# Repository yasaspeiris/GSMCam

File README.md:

# GSMCam
A Python program to determine the Grams per Square Meter of a Fabric using hardware accelerated Image Processing
(Also contains source code, design files and PCB schematics for cartesian slider system used to move the camera across fabrics.)

Conventional method of fabric GSM measurement involves cutting a small round piece of fabric with an area of 0.01 square centimeters and measuring its weight using a precision balance.This project was aimed to replace this conventional method with an optical based one. Currently the scope of the project is limited to single light color (white) fabrics with a plain, twill weave. (Algorithm can also be applied to knit fabrics with a considerable accuracy as well)

For anyone looking to implement a hardware accelerated application with minimal development and debugging time, PYNQ is a great option. Currently PYNQ supports several boards including the Ultra96. The computer vision library for PYNQ provides several overlays for accelerating OpenCV functions in hardware. Currently Filter2D and dilation operations are supported. 

The following flow diagram depicts the stages in the GSM Determination process.

The GUI is made using Flask, and can be used to calibrate and view results.

### Complete Instructions : 
https://www.hackster.io/yasaspeiris/fabric-gsm-determination-using-ultra96-pynq-6c5499

### Contributors : 

Pasindu Liyanage

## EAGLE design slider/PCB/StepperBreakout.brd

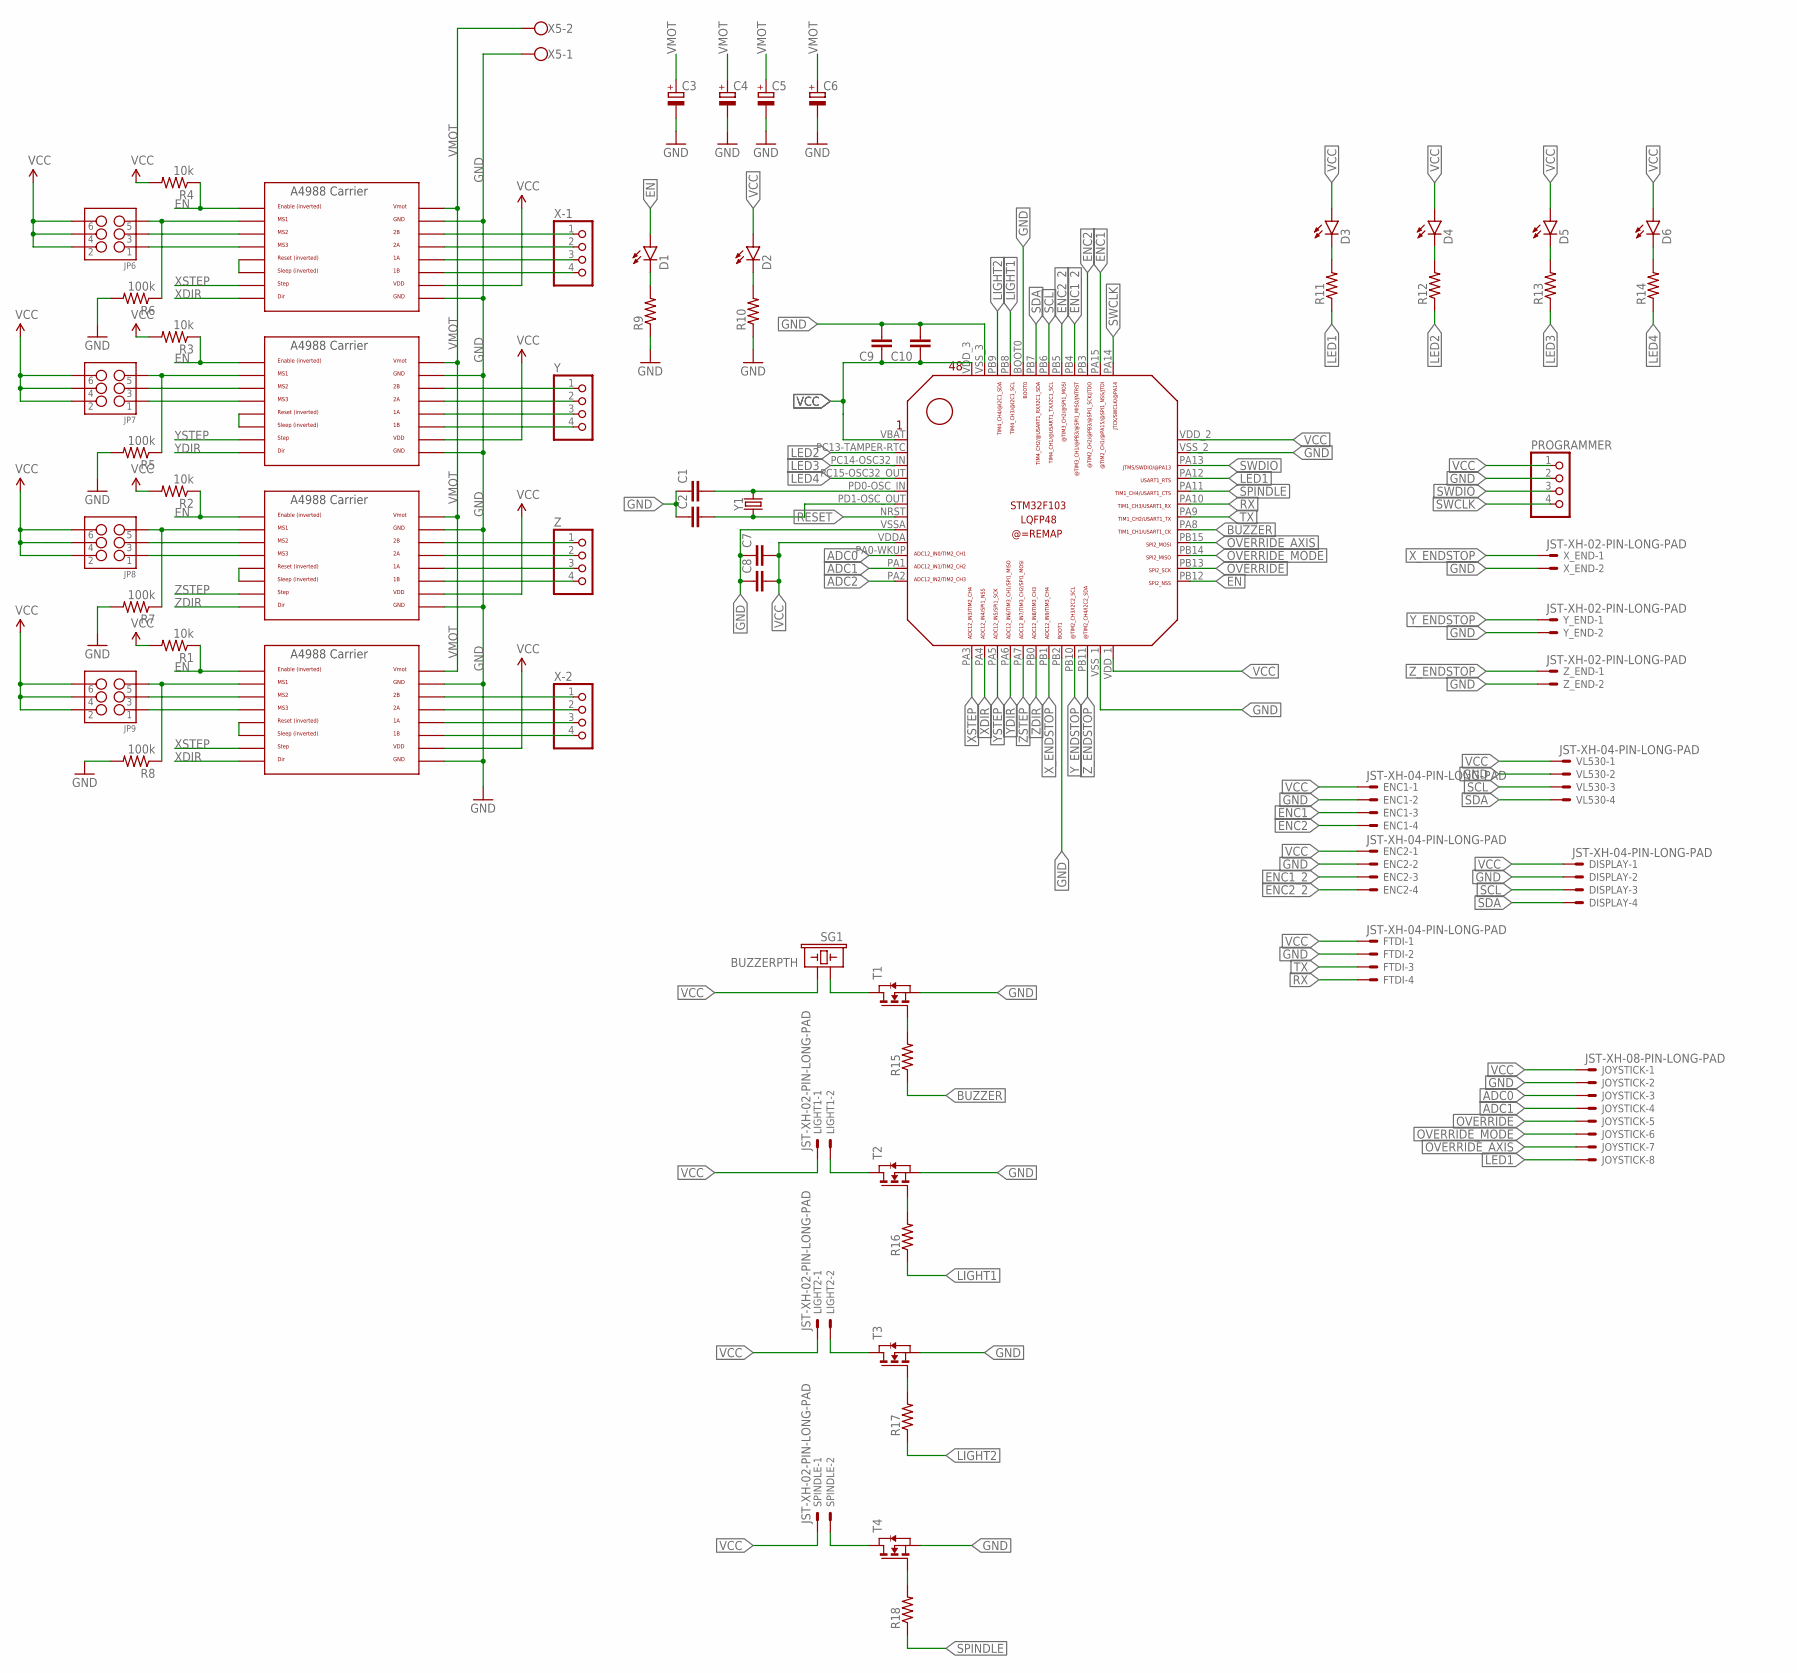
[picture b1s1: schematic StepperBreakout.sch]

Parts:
C1, C2, C7, C8, C9, C10: C-EUC0805; C0805
C3, C4, C5, C6: CPOL-EUE5-8.5; E5-8,5
D1, D2, D3, D4, D5, D6: LED0603; LED-0603
DISPLAY: JST-XH-04-PIN-LONG-PAD; JST-XH-04-PACKAGE-LONG-PAD
ENC1, ENC2: JST-XH-04-PIN-LONG-PAD; JST-XH-04-PACKAGE-LONG-PAD
FTDI: JST-XH-04-PIN-LONG-PAD; JST-XH-04-PACKAGE-LONG-PAD
JOYSTICK: JST-XH-08-PIN-LONG-PAD; JST-XH-08-PACKAGE-LONG-PAD
JP6, JP7, JP8, JP9: M03X2NO_SILK; 2X3-NS
LIGHT1, LIGHT2: JST-XH-02-PIN-LONG-PAD; JST-XH-02-PACKAGE-LONG-PAD
PROGRAMMER: PINHD-1X4; 1X04
R1, R2, R3, R4: 10k; 0805
R5, R6, R7, R8: 100k; 0805
R9, R10, R11, R12, R13, R14, R15, R16, R17, R18: RESISTOR0805-RES; 0805
SG1: BUZZERPTH; BUZZER-12MM
SPINDLE: JST-XH-02-PIN-LONG-PAD; JST-XH-02-PACKAGE-LONG-PAD
T1, T2, T3, T4: NMOSSOT23; SOT-23
U$1, U$2, U$3, U$4: POLOLU_A4983CARRIER; A4988BREAKOUT
U$5: STM32F103_LQFP48
VL530: JST-XH-04-PIN-LONG-PAD; JST-XH-04-PACKAGE-LONG-PAD
X5: W237-102
X-1, X-2: PINHD-1X4; 1X04
X_END: JST-XH-02-PIN-LONG-PAD; JST-XH-02-PACKAGE-LONG-PAD
Y: PINHD-1X4; 1X04
Y1: CRYSTALPTH-HC49UV; HC49U
Y_END: JST-XH-02-PIN-LONG-PAD; JST-XH-02-PACKAGE-LONG-PAD
Z: PINHD-1X4; 1X04
Z_END: JST-XH-02-PIN-LONG-PAD; JST-XH-02-PACKAGE-LONG-PAD

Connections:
ADC0: JOYSTICK.3, U$5.PA0-WKUP
ADC1: JOYSTICK.4, U$5.PA1
ADC2: U$5.PA2
BUZZER: R15.1, U$5.PA8
EN: D1.A, R1.1, R2.1, R3.1, R4.1, U$1.EN, U$2.EN, U$3.EN, U$4.EN, U$5.PB12
ENC1: ENC1.3, U$5.PA15
ENC1_2: ENC2.3, U$5.PB4
ENC2: ENC1.4, U$5.PB3
ENC2_2: ENC2.4, U$5.PB5
GND: C1.1, C2.1, C3.-, C4.-, C5.-, C6.-, C7.1, C8.1, C9.2, C10.2, DISPLAY.2, ENC1.2, ENC2.2, FTDI.2, JOYSTICK.2, PROGRAMMER.2, R5.2, R6.2, R7.2, R8.2, R9.1, R10.1, T1.2 (S), T2.2 (S), T3.2 (S), T4.2 (S), U$1.GND, U$1.GND@0 (GND), U$2.GND, U$2.GND@0 (GND), U$3.GND, U$3.GND@0 (GND), U$4.GND, U$4.GND@0 (GND), U$5.BOOT0, U$5.PB2, U$5.VSSA, U$5.VSS_1, U$5.VSS_2, U$5.VSS_3, VL530.2, X5.1, X_END.2, Y_END.2, Z_END.2
LED1: JOYSTICK.8, R11.1, U$5.PA12
LED2: R12.1, U$5.PC13-TAMPER-RTC
LED3: R13.1, U$5.PC14-OSC32_IN
LED4: R14.1, U$5.PC15-OSC32_OUT (PC15-OSC_OUT)
LIGHT1: R16.1, U$5.PB8
LIGHT2: R17.1, U$5.PB9
unnamed: U$3.1B, Y.4
unnamed: U$3.1A, Y.3
unnamed: U$3.2A, Y.2
unnamed: U$3.2B, Y.1
unnamed: U$1.2B, Z.1
unnamed: U$1.2A, Z.2
unnamed: U$1.1A, Z.3
unnamed: U$1.1B, Z.4
unnamed: U$2.2B, X-2.1
unnamed: U$2.2A, X-2.2
unnamed: U$2.1A, X-2.3
unnamed: U$2.1B, X-2.4
unnamed: U$4.2B, X-1.1
unnamed: U$4.2A, X-1.2
unnamed: U$4.1A, X-1.3
unnamed: U$4.1B, X-1.4
unnamed: JP6.5, R6.1, U$4.MS1
unnamed: JP6.3, U$4.MS2
unnamed: JP6.1, U$4.MS3
unnamed: JP7.5, R5.1, U$3.MS1
unnamed: JP7.3, U$3.MS2
unnamed: JP7.1, U$3.MS3
unnamed: JP8.5, R7.1, U$1.MS1
unnamed: JP8.3, U$1.MS2
unnamed: JP8.1, U$1.MS3
unnamed: JP9.5, R8.1, U$2.MS1
unnamed: JP9.3, U$2.MS2
unnamed: JP9.1, U$2.MS3
unnamed: C1.2, U$5.PD0-OSC_IN, Y1.2
unnamed: D1.C, R9.2
unnamed: D2.C, R10.2
unnamed: C2.2, U$5.PD1-OSC_OUT, Y1.1
unnamed: U$2.RST, U$2.SLP (SLEEP)
unnamed: U$1.RST, U$1.SLP (SLEEP)
unnamed: U$3.RST, U$3.SLP (SLEEP)
unnamed: U$4.RST, U$4.SLP (SLEEP)
unnamed: D3.C, R11.2
unnamed: D4.C, R12.2
unnamed: D5.C, R13.2
unnamed: D6.C, R14.2
unnamed: SG1.+ (1), T1.1 (D)
unnamed: R15.2, T1.3 (G)
unnamed: LIGHT1.2, T2.1 (D)
unnamed: R16.2, T2.3 (G)
unnamed: LIGHT2.2, T3.1 (D)
unnamed: R17.2, T3.3 (G)
unnamed: SPINDLE.2, T4.1 (D)
unnamed: R18.2, T4.3 (G)
OVERRIDE: JOYSTICK.5, U$5.PB13
OVERRIDE_AXIS: JOYSTICK.7, U$5.PB15
OVERRIDE_MODE: JOYSTICK.6, U$5.PB14
RESET: U$5.NRST
RX: FTDI.4, U$5.PA10
SCL: DISPLAY.3, U$5.PB6, VL530.3
SDA: DISPLAY.4, U$5.PB7, VL530.4
SPINDLE: R18.1, U$5.PA11
SWCLK: PROGRAMMER.4, U$5.PA14
SWDIO: PROGRAMMER.3, U$5.PA13
TX: FTDI.3, U$5.PA9
VCC: C7.2, C8.2, C9.1, C10.1, D2.A, D3.A, D4.A, D5.A, D6.A, DISPLAY.1, ENC1.1, ENC2.1, FTDI.1, JOYSTICK.1, JP6.2, JP6.4, JP6.6, JP7.2, JP7.4, JP7.6, JP8.2, JP8.4, JP8.6, JP9.2, JP9.4, JP9.6, LIGHT1.1, LIGHT2.1, PROGRAMMER.1, R1.2, R2.2, R3.2, R4.2, SG1.- (2), SPINDLE.1, U$1.VDD, U$2.VDD, U$3.VDD, U$4.VDD, U$5.VBAT, U$5.VDDA, U$5.VDD_1, U$5.VDD_2, U$5.VDD_3, VL530.1
VMOT: C3.+, C4.+, C5.+, C6.+, U$1.VMOT, U$2.VMOT, U$3.VMOT, U$4.VMOT, X5.2
XDIR: U$2.DIR, U$4.DIR, U$5.PA4
XSTEP: U$2.STEP, U$4.STEP, U$5.PA3
X_ENDSTOP: U$5.PB1, X_END.1
YDIR: U$3.DIR, U$5.PA6
YSTEP: U$3.STEP, U$5.PA5
Y_ENDSTOP: U$5.PB10, Y_END.1
ZDIR: U$1.DIR, U$5.PB0
ZSTEP: U$1.STEP, U$5.PA7
Z_ENDSTOP: U$5.PB11, Z_END.1

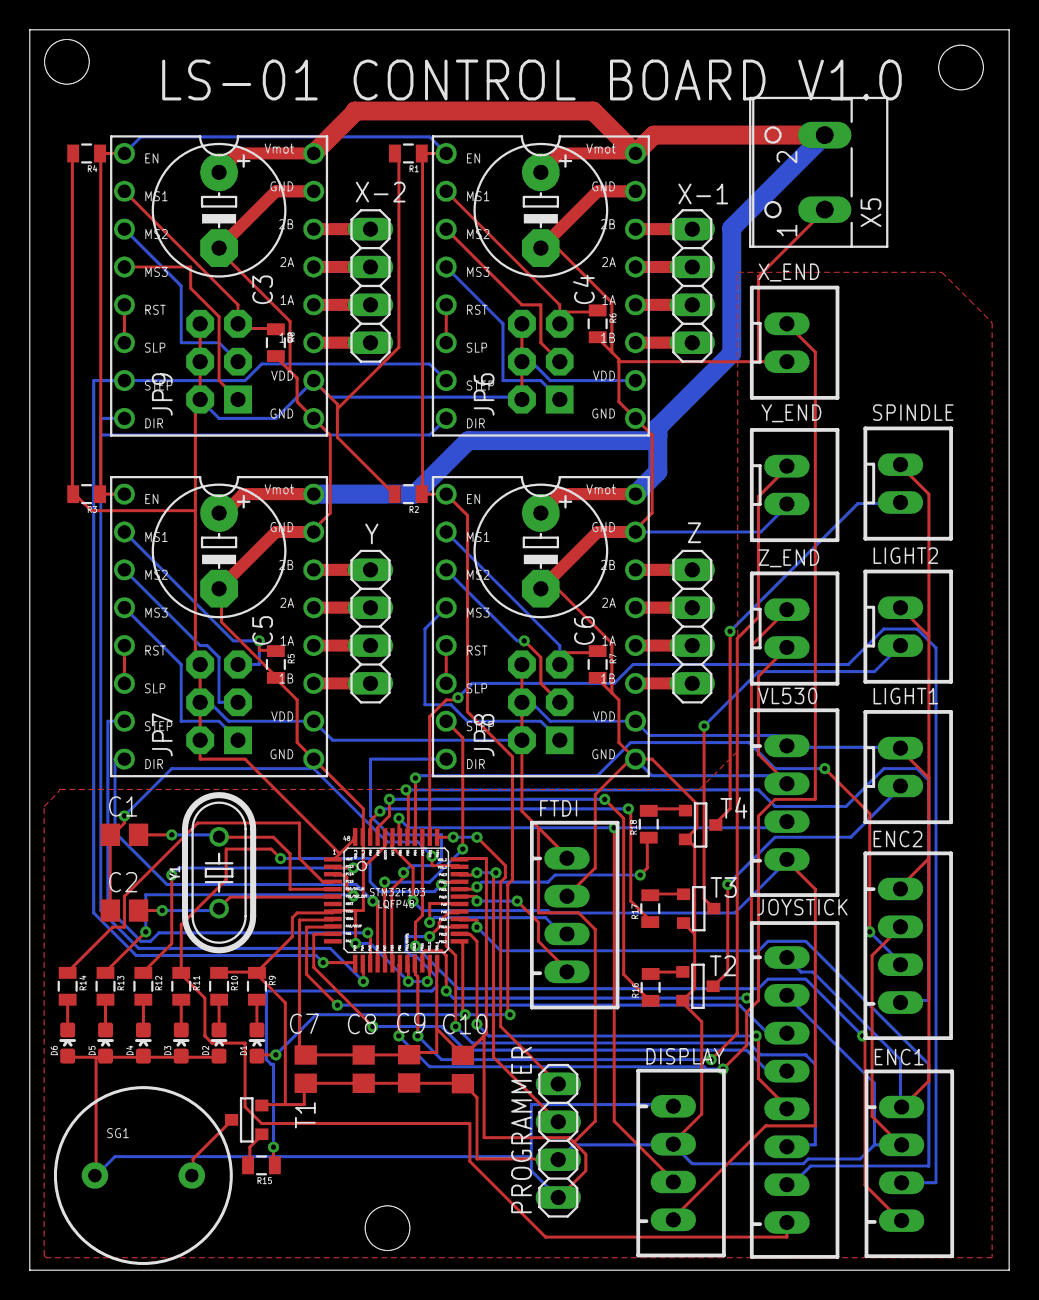
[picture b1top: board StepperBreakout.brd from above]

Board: 2 copper layers, 65.7 x 83.2 mm, 67 parts (0 on the bottom side), 84 nets.

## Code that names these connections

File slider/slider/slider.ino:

//Limit Switches
#define XLIMIT PB1 //Limit switches must be Normally Open and connected to GND.
#define YLIMIT PB10
#define ZLIMIT PB11

#define XSTEP PA3
#define XDIR PA4

#define YSTEP PA5
#define YDIR PA6

#define ZSTEP PA7
#define ZDIR PB0

#define ENABLE PB12

#define XMOTORACC 500
#define XMOTORMAXSPEED 800

#define YMOTORACC 1000
#define YMOTORMAXSPEED 1000

#define ZMOTORACC 1000
#define ZMOTORMAXSPEED 1000

#define X_PER_MM 5
#define Y_PER_MM 5
#define Z_PER_MM 100

#define X_MAX 200
#define Y_MAX 200
#define Z_MAX 400

#include <AccelStepper.h>

AccelStepper XMOTOR(1,XSTEP,XDIR);
AccelStepper YMOTOR(1,YSTEP,YDIR);
AccelStepper ZMOTOR(1,ZSTEP,ZDIR);


//=====[ CONSTANTS ]============================================================
#define   DEBUG   0   // 0 = debugging disabled, 1 = enabled
#define ENABLE_ACTUATORS 1 //Set to one to make steppers move according to serial input

//=====[ VARIABLES ]============================================================

String readString; //main captured String 
int Xval = 0; //Absolute positions of X,Y,Z. 
int Yval = 0;
int Zval = 0;
int func = 0;

int ind1; // , location indexes for serial parse
int ind2;
int ind3;
int ind4;

void setup() {
  // put your setup code here, to run once:
  Serial1.begin(9600);
  Serial1.setTimeout(1);
  pinsetup();
  for (int i = 0; i<5; i++){
    tone(PA8, 31, 300);
    delay(200);
    tone(PA8, 61, 300);
    delay(200);
  }
  
  delay(2000);
  autohome(); //I've disabled autohome for now.

}

void loop() {
  //=====[ IMPORTANT ]============================================================
  //Your input string must use , as the data delimiter and * as the line delimeter. Eg - to move X to 2 Y to 5 and Z to 10 and grabber to 20, you should send   2,5,10,20*
  //You can see if its correct by setting DEBUG to 1 and looking at the output.
  //Set ENABLE_ACTUATORS to enable movement of steppers.
  //Once you're sure about the movement and directions, test autohome function.
  SerialParser();

  
}

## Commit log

2019-01-25 initial source commit
2021-05-30 Updated cover image

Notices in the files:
parts and their libraries:
SparkFun-LED: Licensing: Creative Commons ShareAlike 4.0 International - https://creativecommons.org/licenses/by-sa/4.0
SparkFun: Licensing: CC v3.0 Share-Alike You are welcome to use this library for commercial purposes.
